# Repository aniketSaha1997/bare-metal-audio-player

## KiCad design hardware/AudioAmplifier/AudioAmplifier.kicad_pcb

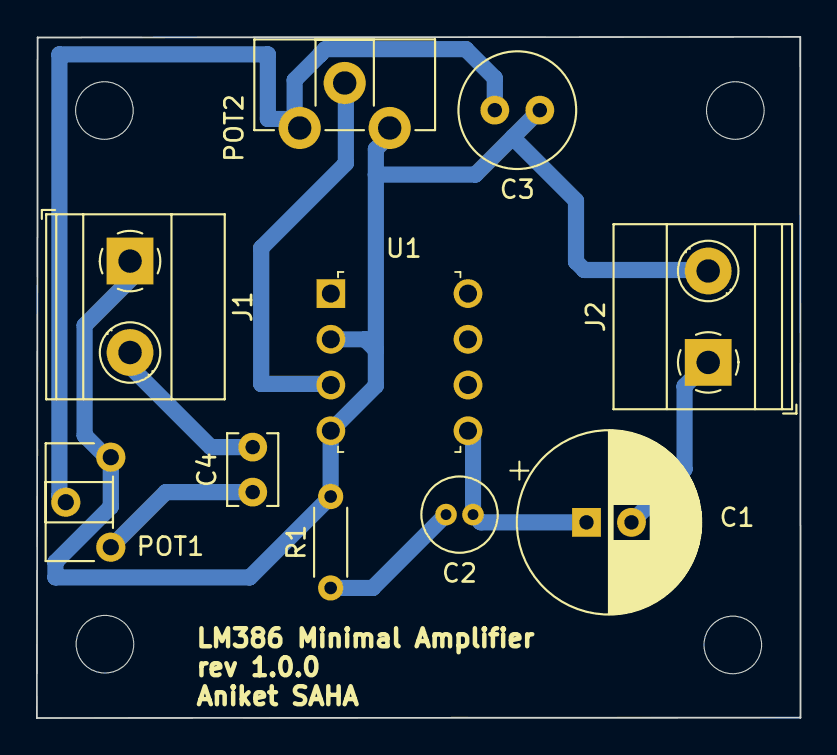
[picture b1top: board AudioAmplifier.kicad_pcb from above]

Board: 2 copper layers, 42.4 x 37.8 mm, 10 parts (0 on the bottom side), 8 nets.

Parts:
C1: 1000uF; CP_Radial_D10.0mm_P2.50mm
C2: 0.1 uF; C_Radial_D4.0mm_H5.0mm_P1.50mm
C3: 100 nF; C_Radial_D6.3mm_H5.0mm_P2.50mm
C4: 4.7uF; C_Disc_D3.8mm_W2.6mm_P2.50mm
J1, J2: Screw_Terminal_01x02; TerminalBlock_Phoenix_MKDS-1,5-2-5.08_1x02_P5.08mm_Horizont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
POT1: 10K; Potentiometer_ACP_CA6-H2,5_Horizontal
POT2: 10K; Potentiometer_ACP_CA9-H2,5_Horizontal
R1: 10R; R_Axial_DIN0204_L3.6mm_D1.6mm_P5.08mm_Horizontal
U1: LM386; DIP-8_W7.62mm

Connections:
GND: C3.1, J1.1, J2.2, POT1.3, POT2.3, R1.2, U1.2 (-), U1.4 (GND)
unnamed: C1.1, C2.1, U1.5
unnamed: C1.2, J2.1
unnamed: C2.2, R1.1
unnamed: C3.2, POT1.2, POT2.1
unnamed: C4.2, J1.2
unnamed: C4.1, POT1.1
unnamed: POT2.2, U1.3 (+)

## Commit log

2024-04-05 Added simple amplifier pcb design
2024-04-05 Added gitignore condition for backup files
2024-04-07 Added RC filter into the circuit. Not yet changed THT footprints yet
2024-04-08 Added ground plain and increased track size, changed capacitor size
2024-04-24 Added project file for nucleo F7 for audio player from flash audio
2024-04-24 Updated gitignore
